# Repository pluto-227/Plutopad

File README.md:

# Plutopad
This is a Case, Schematic, PCB, and Firmware for my Plutopad. It is a macropad with 9 switch keys, a Rotary Encoder Switch, and an OLED screen.

This is the finished product of the assembled pad.

Above is the schematic used to create the PCB.

This is the PCB.

This is the final case by itself.

[PlutoPad.csv](https://github.com/user-attachments/files/28865083/PlutoPad.csv)

"Reference","Qty","Value","DNP","Exclude from BOM","Exclude from Board","Footprint","Datasheet"
"D1,D2,D3,D4,D5,D6,D7,D8,D9","9","1N4148","","","","Diode_THT:D_DO-35_SOD27_P7.62mm_Horizontal","https://assets.nexperia.com/documents/data-sheet/1N4148_1N4448.pdf"
"J1","1","Conn_01x04","","","","Display:ER_OLEDM0.91_1x-I2C",""
"SW1,SW2,SW3,SW4,SW5,SW6,SW7,SW8,SW9","9","SW_Push","","","","MINE:MINE",""
"SW17","1","RotaryEncoder_Switch","","","","Rotary_Encoder:RotaryEncoder_Alps_EC11E-Switch_Vertical_H20mm",""
"U1","1","MOUDLE-SEEEDUINO-XIAO","","","","footprintsV1:XIAO-Generic-Hybrid-14P-2.54-21X17.8MM_fixedV2",""
Bill of materials is stated above.

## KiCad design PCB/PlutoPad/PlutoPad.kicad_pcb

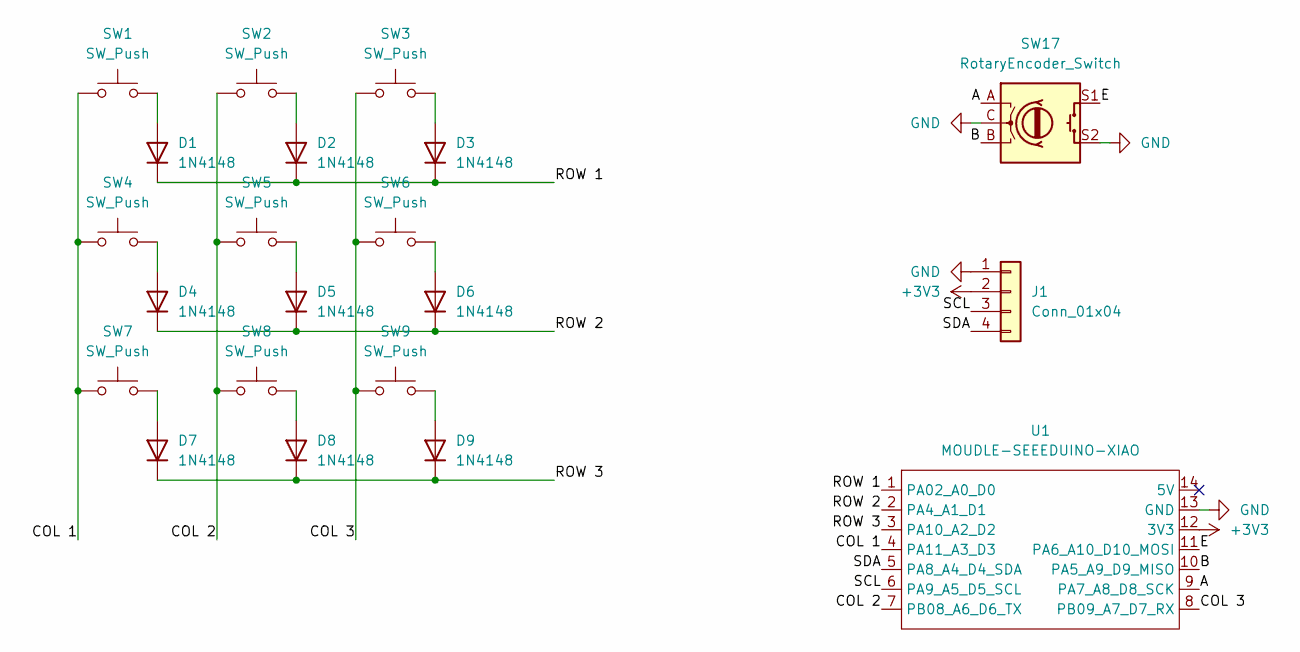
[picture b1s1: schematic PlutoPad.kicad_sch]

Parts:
D1, D2, D3, D4, D5, D6, D7, D8, D9: 1N4148; D_DO-35_SOD27_P7.62mm_Horizontal
J1: Conn_01x04; ER_OLEDM0.91_1x-I2C
SW1, SW2, SW3, SW4, SW5, SW6, SW7, SW8, SW9: SW_Push; MINE
SW17: RotaryEncoder_Switch; RotaryEncoder_Alps_EC11E-Switch_Vertical_H20mm
U1: MOUDLE-SEEEDUINO-XIAO; XIAO-Generic-Hybrid-14P-2.54-21X17.8MM_fixedV2

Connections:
+3V3: J1.2, U1.12 (3V3)
/A: SW17.A, U1.9 (PA7_A8_D8_SCK)
/B: SW17.B, U1.10 (PA5_A9_D9_MISO)
/COL 1: SW1.1, SW4.1, SW7.1, U1.4 (PA11_A3_D3)
/COL 2: SW2.1, SW5.1, SW8.1, U1.7 (PB08_A6_D6_TX)
/COL 3: SW3.1, SW6.1, SW9.1, U1.8 (PB09_A7_D7_RX)
/E: SW17.S1, U1.11 (PA6_A10_D10_MOSI)
/ROW 1: D1.1 (K), D2.1 (K), D3.1 (K), U1.1 (PA02_A0_D0)
/ROW 2: D4.1 (K), D5.1 (K), D6.1 (K), U1.2 (PA4_A1_D1)
/ROW 3: D7.1 (K), D8.1 (K), D9.1 (K), U1.3 (PA10_A2_D2)
/SCL: J1.3, U1.6 (PA9_A5_D5_SCL)
/SDA: J1.4, U1.5 (PA8_A4_D4_SDA)
GND: J1.1, SW17.C, SW17.S2, U1.13 (GND)
unnamed: D1.2 (A), SW1.2
unnamed: D2.2 (A), SW2.2
unnamed: D3.2 (A), SW3.2
unnamed: D4.2 (A), SW4.2
unnamed: D5.2 (A), SW5.2
unnamed: D6.2 (A), SW6.2
unnamed: D7.2 (A), SW7.2
unnamed: D8.2 (A), SW8.2
unnamed: D9.2 (A), SW9.2

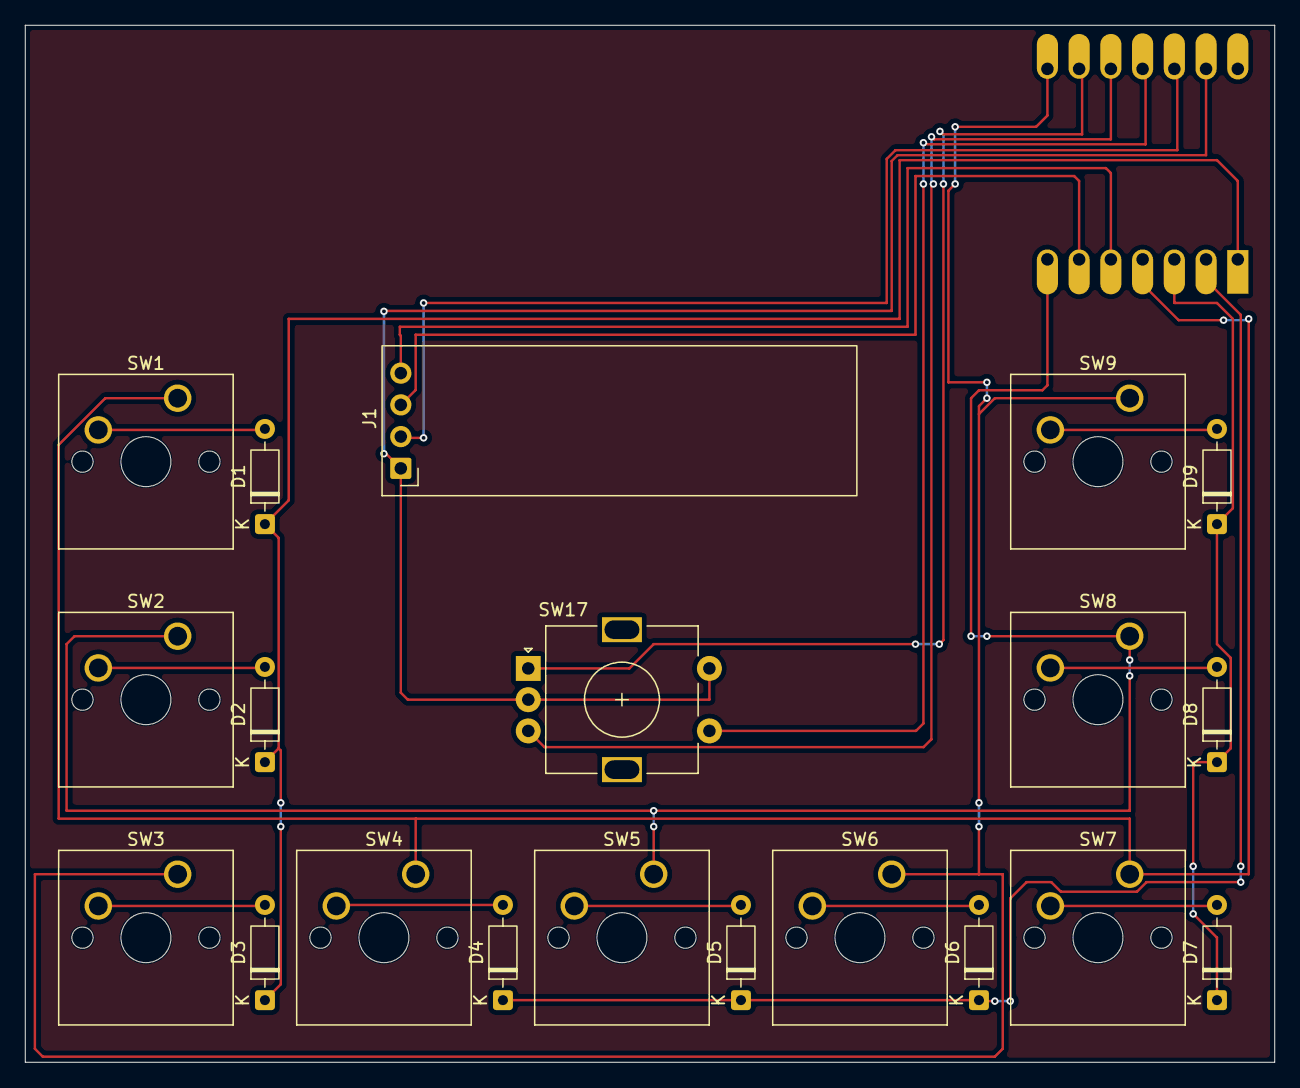
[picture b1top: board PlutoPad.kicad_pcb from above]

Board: 2 copper layers, 100.0 x 83.0 mm, 21 parts (1 on the bottom side), 22 nets.

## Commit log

2026-06-06 Create CAD
2026-06-12 Enhance README with detailed Plutopad description and images
    Updated the description of the Plutopad to include details about its components and added images of the assembled product, schematic, PCB, and case. Included a bill of materials.
2026-06-12 Update README with additional images and CSV link
2026-06-12 Update CAD
2026-06-12 Add JSON configuration for hostname and username
2026-06-12 Update PCB
2026-06-12 Add new PCB configuration with design settings
    This commit adds a new PCB configuration file with various design settings, rules, and metadata for the PCB layout.
2026-06-12 Add firmware for Pluto Pad with OLED support
    Initial implementation of Pluto Pad firmware with OLED display support and layout mapping.
2026-06-12 Firmware for Plutopad
2026-06-12 Full assembly for Plutopad .step
2026-06-12 PCB project
2026-06-12 Firmware Source
2026-06-12 Files needed for production
